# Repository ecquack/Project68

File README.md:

# Project68

Project68 is a Motorola MC68xxx 16/32 bit single board computer with an 8 bit PIC18 co-processor. 

My goal was to do something interesting with the tube of factory new 68008 CPUs that I've been hoarding for 25 years, 
so I have designed a useful self contained 68K computer using a minumum number of components and special tools.

The system connects directly to a monitor and keyboard and does not require a host computer.

This project is at an early stage of development, but it is intended to run uCLinux 4.4.

Special thanks to [*crmaykish*](https://github.com/crmaykish), creator of the [Mackerel-68K](https://github.com/crmaykish/mackerel-68k) project.

## Project68 features

- MC68008FN8 CPU clocked at 7.16 mHz
- 4 megabytes of SRAM
- Optional overclocking to 14.31818 mHz
- PIC18F87J11 co-processor clocked at 14.31818 mHz (57.27 mHz internal w/4X PLL)
- 80x25 character monochrome ASCII video display (NTSC composite video)
- PS/2 keyboard interface
- TTL/USB serial port
- micro-SD card socket
- Audio Speaker for ASCII “bell” sound
- **No PAL/GAL/CPLD/FPGA programmable logic required**
- Only two LVTTL parts required.
- Expansion ports for a dual serial card and a non-volatile RTC

## OPERATING REQUIREMENTS

- TV or Monitor with composite video input (NTSC)
- PS/2 keyboard
- 5V 1A power supply with USB-C cable (phone charger)
- SD card with uCLinux image

## CPU

The CPU is the 8 bit external bus version of the 68K, the MC68008FN8. It comes in the larger 52 pin PLCC package which can address up to 4 megabytes of memory. The CPU is socketed on the board so that you can use an automated assembly service such as JLC PCB or PCBWAY for all the soldering if you prefer. This is a 16/32 bit CPU internally with a narrow external bus which allows using byte wide external memories.

The parts I have are rated at 8mHz, but 10mHz parts are also available (MC68000FN10). In order to provide an NTSC video clock, the processor runs at ~7.16mHz. Either speed part can (usually) be successfully overclocked to ~14.318mHz without issue. An overclocking jumper is provided if you feel the need for speed.

## MEMORY

The system has four megabytes of memory. It uses a single 32 megabit 4Mx8 55ns SRAM chip. This fills the *entire* available address space with SRAM. There is no separate FLASH, EPROM, or ROM memory, no address decoding of any kind,  no special address hardware at reset, and no traditional memory mapped I/O. Just an unbroken sea of RAM from 0-0x3FFFFF and a simple _DTACK generator. 

The SRAM part is a fairly pricey Renesas RMLV3216AGSA-5S2 sourced from Digikey. You can also use the pin compatible Alliance AS6C6416-55TIN from Mouser which is a 64 megabit part, which is actually cheaper, but you will only be utilizing half the memory.

The memory and the PIC18 run at 3.3 volts (there is an LDO regulator on the board). The 5 volt MC68008  has a logic high level of 2.4 volts, which might be safe to use with these parts. I may end up using level shifters, but they eat 20 nanoseconds from the bus cycle. Stay tuned for my experimental results.

## CO-PROCESSSOR

The PIC18F87J11 microcontroller comes in an 80 pin TQFP package. This part was chosen because it has enough GPIO pins to emulate the entire MC68008 bus. It has 128K of FLASH memory, and just under 4K of on chip SRAM.

**The PIC18 co-processor provides all the main processor’s I/O using soft-DMA.** When it is time to transfer data to or from the processor, the co-processor requests the bus from the 68008. When the bus is granted, it uses bit-banging DMA to read and write the SRAM. A few specific addresses in the memory space are designated as I/O command and status registers and are interpreted as such by the co-processor to provide low level BIOS functions for the console, serial port, and SD card. 

At power up the co-processor asserts _HALT and _RESET and then copies up to 64K of BIOS into the SRAM from the upper half of FLASH memory that’s built into the PIC18. It then releases the 68K bus and the MC68008 starts.

## VIDEO DISPLAY

**The co-processor is also responsible for generating the 80x25 video display.** This is done with a *really* tight  horizontal sync interrupt handler written in assembly language. It uses an interleaved character FLASH lookup table with an 8x8 pixel font. One EUSART on the PIC18 is used as a video shift register (nice!), which makes it possible to clock pixels out once per instruction cycle.

Roughly half of the PIC18's SRAM (2K) is dedicated to the video display.

The physical video interface consists of two output pins and a two resistor network that is connected to an RCA jack. One pin is the output of the synchronous serial transmitter, and the other is the software generated sync line, used for both horizontal and vertical sync.

The video display is not interlaced and does not include a colorburst. The 8x8 ROM font consists of the standard printable ASCII characters (codes 32-126), plus a number of special characters (codes 0-31 and 127). The upper 128 characters are reverse video of the lower 128 characters, which is used to generate the cursor. There are no fancy effects like blink, underscore, or dim. There are no code page 437 special characters.

Most of the co-processor's time is spent generating video. There is a short horizontal blanking period at the end of each line, and there is a longer vertical blanking interval at the end of each video field during which the processor is free to perform other tasks. All video generation (and PS/2 keyboard processing) takes place inside the interrupt handler.

Note that it should be possible to run a PAL monitor instead of NTSC by simply adjusting the timing #DEFINE statements in the beginning of *80columnvideo.h*.
I do not have a monitor that accepts PAL video to test this with.

## PS/2 INTERFACE

The system uses the PIC18 MSSP (synchronous serial port) in slave mode with an assembly language interrupt handler to interface to the PS/2 keyboard. 
The interrupt handler runs during horizontal blanking, and always takes the same number of clock cycles to run, no matter which code path is taken, to avoid disturbing the video output. 

When characters arrive on the PS/2 keyboard or serial port, the co-processor requests the bus, and stores the received characters into a software FIFO in SRAM.

## SD CARD

The SD card socket is connected to the PIC18 over the shared SPI bus. 512 bytes of PIC18 SRAM is reserved to store a single block of data to/from the SD card. 

## BIOS

The BIOS provides a few functions to access the console, the serial port, and the SD card. It also loads and starts Linux from the SD card. Additional functions could be added, for example, to copy the entire screen buffer to and from memory, give control over the PWM audio output beyond the fixed "beep", or to support additional SPI devices such as a non-volatile real time clock. 

## TIMER INTERRUPT

The vertical blanking signal serves as a periodic timer interrupt (60 hertz) to the 68008. This is used by the BIOS for communication and by the Linux kernel for timekeeping and task switching. 

## USB/TTL SERIAL PORT

A CH340N provides a very basic serial port connection to a USB host system. The USB C connector also provides power to the board. There is also a header with jumpers that allow the TTL serial lines to be disconnected from the USB chip and used directly. 

## EXPANSION PORTS

There are two main expansion ports. Each has power, SPI bus, it's own SPI chip select, it's own interrupt line, and two GPIO pins. My intention is to use an SPI DUAL UART on one port and an SPI RTC on the other. Supporting these will require additions to the BIOS. The interrupt line and the chip select can be used as GPIOs if the SPI bus is not used, but MISO, MOSI, and SCLK are shared with the SD card socket and cannot be reassigned.

There is also a third expansion port which brings out the three unused PIC18 GPIO pins, power, and ground. Two of these pins are on port B and can be used as interrupt sources.

## ICSP PORT

For programming the PIC MCU, this 6 pin connector contains PGD, PGC, _MCLR, +5V, and GND.

## PERFORMANCE NOTES

The current system was designed to see how simply a complete 68K computer system could be made, and it uses a minimum number of parts for a system that has its own video and keyboard interfaces. By adding just a few chips you can dramatically increase the performance of the system.

For higher overall system performance you could use a second smaller PIC18 (such as a PIC18F26K22) dedicated to generating video. Right now there is an I/O bottleneck because I/O operations are only performed during video blanking.

A decoded address that causes an interrupt on the PIC18 would eliminate the need for the PIC18 to poll the MC68008's memory. Again, this would increase performance but it would add chips to the design and eat into the memory address space. Two 74HCT30s and a 74HCT00 would suffice, and would eat only 64 bytes from the memory map. 

## BUILD REQUIREMENTS
 
- PIC programmer for initial programming (you can build a very simple bit-banging programmer using a repurposed Arduino)
- Computer system with MicroSD card interface for preparing the SD card.
- CCS PICC C Compiler (optional - pre-built binaries are available)*
- X86 Linux system (optional - a pre-built binary is available)
- KiCAD (optional - Gerber files are provided)

*note that there is a 45 day free trial of this compiler.

## Pre-assembled boards

I started out with a tube full of sixteen 68008 parts that I got from a Motorola rep back in the '90s. I'm keeping a few chips for myself and my friends, but 
I may have a few pre-assembled boards complete with CPUs and SD cards for sale at some point. 

Note that the MC68008FN is no longer in production, but at this time (August, 2025) it is not difficult to find them on eBay for around USD$30 with shipping. 

## PROJECT STATUS

The schematic capture and layout of the first version is complete. I'll order the blank boards and stencil from JLCPCB next.

I wrote the PIC18 80 column video code and the PS/2 keyboard handler code back in 2010 and posted them to the CCS C compiler forum. They were tested on a single sided PIC18F26J11 board that I milled on my CNC machine back in the day.

Once the layout is complete I plan to have a pair of assembled boards made for my by JLCPCB.

After that, the next debugging steps are:

0. Blink the LED
1. Get the video display running
2. test the keyboard port
3. bit-bang the memory interface to read and write from the SRAM
4. load a small test program into the 68K and start it
5. read and write a block from the SD card

Then comes the work of writing the BIOS and building the linux image.

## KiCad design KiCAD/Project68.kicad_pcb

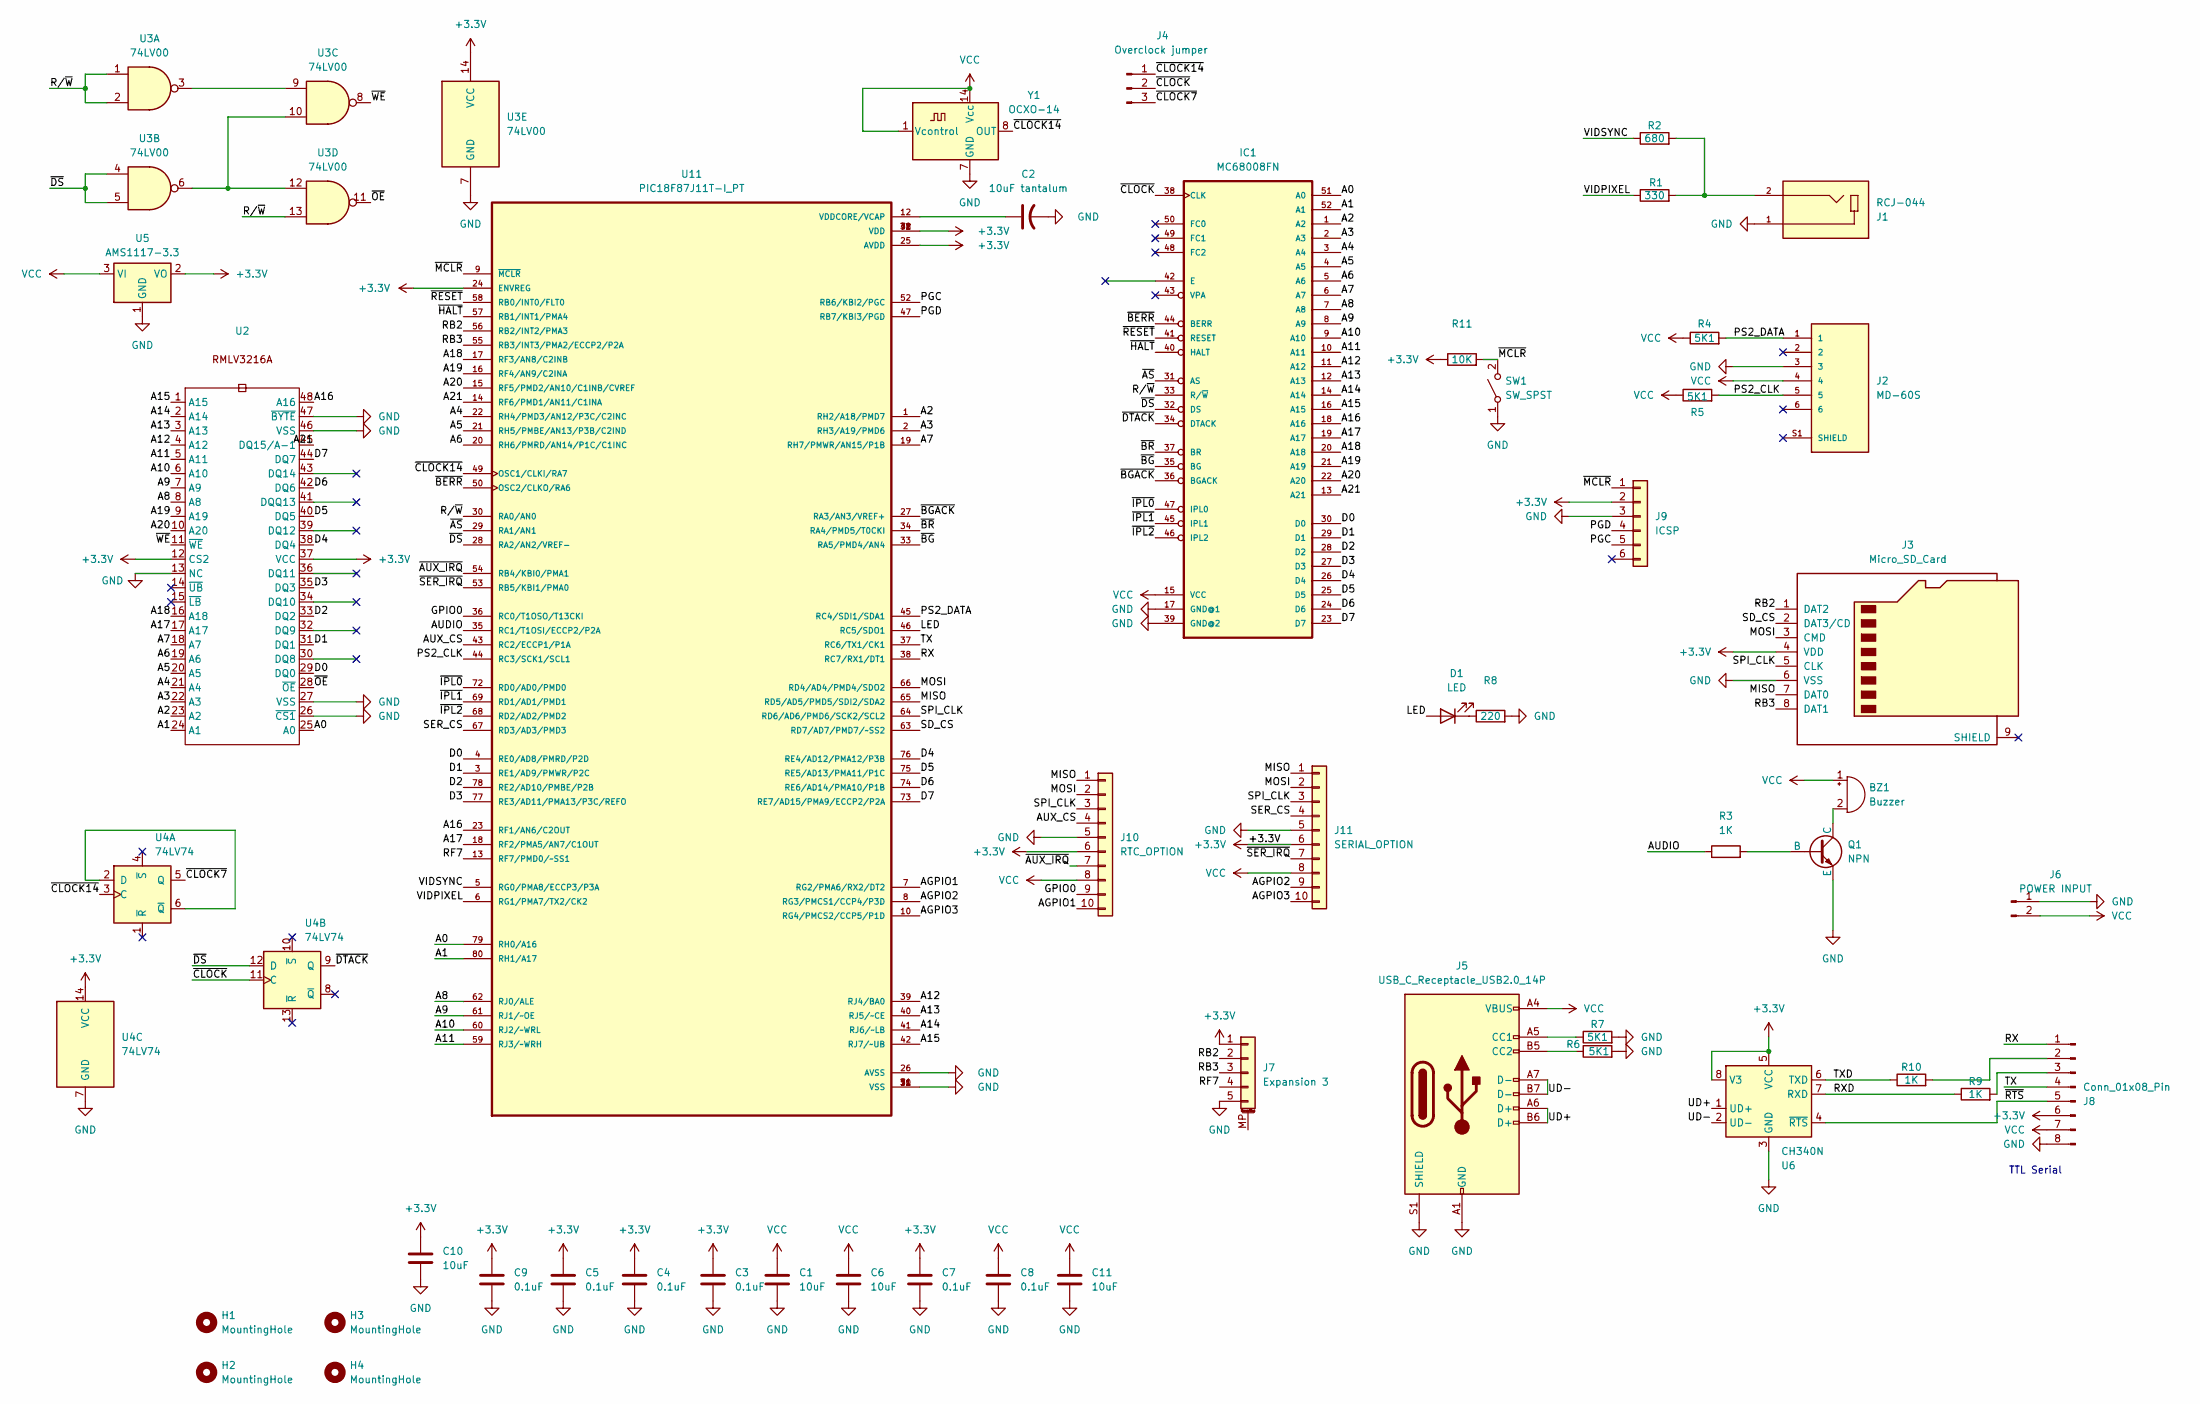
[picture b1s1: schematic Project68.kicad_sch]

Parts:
BZ1: Buzzer; MURATA
C1, C6, C10, C11: 10uF; C_1206_3216Metric
C2: 10uF tantalum; C_1206_3216Metric
C3, C4, C5, C7, C8, C9: 0.1uF; C_1206_3216Metric
D1: LED; LED_1206_3216Metric
H1, H2, H3, H4: MountingHole; MountingHole_3.2mm_M3
IC1: MC68008FN; PLCC52-S
J1: RCJ-044; CUI_RCJ-044; PARTREV 1.02
J2: MD-60S; CUI_MD-60S; PARTREV 02/18/2022
J3: Micro_SD_Card; microSD_HC_Molex_47219-2001
J4: Overclock jumper; PinHeader_1x03_P2.54mm_Vertical
J5: USB_C_Receptacle_USB2.0_14P; USB_C_Receptacle_GCT_USB4105-xx-A_16P_TopMnt_Horizontal
J6: POWER INPUT; PinHeader_1x02_P2.54mm_Vertical
J7: Expansion 3; PinHeader_1x05_P2.54mm_Vertical
J8: Conn_01x08_Pin; PinHeader_1x08_P2.54mm_Vertical
J9: ICSP; PinHeader_1x06_P2.54mm_Vertical
J10: RTC_OPTION; PinHeader_1x10_P2.54mm_Vertical
J11: SERIAL_OPTION; PinHeader_1x10_P2.54mm_Vertical
Q1: NPN; SOT-23-3
R1: 330; R_1206_3216Metric
R2: 680; R_1206_3216Metric
R3, R9, R10: 1K; R_1206_3216Metric
R4, R5, R6, R7: 5K1; R_1206_3216Metric
R8: 220; R_1206_3216Metric
R11: 10K; R_1206_3216Metric
SW1: SW_SPST; SW_Push_1P1T_NO_CK_KMR2
U2: TSOP-I-48_18.4x12mm_P0.5mm
U3: 74LV00; SOIC-14_3.9x8.7mm_P1.27mm
U4: 74LV74; SOIC-14_3.9x8.7mm_P1.27mm
U5: AMS1117-3.3; SOT-223-3_TabPin2
U6: CH340N; SOP-8_3.9x4.9mm_P1.27mm
U11: PIC18F87J11T-I_PT; QFP50P1400X1400X120-80N
Y1: OCXO-14; Oscillator_DIP-14

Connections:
+3.3V: C3.1, C4.1, C5.1, C7.1, C9.1, C10.1, J3.4 (VDD), J7.1, J8.6, J9.2, J10.6, J11.6, R11.1, U2.12 (CS2), U2.37 (VCC), U3.14 (VCC), U4.14 (VCC), U5.2 (VO), U6.5 (VCC), U6.8 (V3), U11.24 (ENVREG), U11.25 (AVDD), U11.32 (VDD), U11.48 (VDD), U11.71 (VDD)
/A0: IC1.51 (A0), U2.25 (A0), U11.79 (RH0/A16)
/A1: IC1.52 (A1), U2.24 (A1), U11.80 (RH1/A17)
/A2: IC1.1 (A2), U2.23 (A2), U11.1 (RH2/A18/PMD7)
/A3: IC1.2 (A3), U2.22 (A3), U11.2 (RH3/A19/PMD6)
/A4: IC1.3 (A4), U2.21 (A4), U11.22 (RH4/PMD3/AN12/P3C/C2INC)
/A5: IC1.4 (A5), U2.20 (A5), U11.21 (RH5/PMBE/AN13/P3B/C2IND)
/A6: IC1.5 (A6), U2.19 (A6), U11.20 (RH6/PMRD/AN14/P1C/C1INC)
/A7: IC1.6 (A7), U2.18 (A7), U11.19 (RH7/PMWR/AN15/P1B)
/A8: IC1.7 (A8), U2.8 (A8), U11.62 (RJ0/ALE)
/A9: IC1.8 (A9), U2.7 (A9), U11.61 (RJ1/~OE)
/A10: IC1.9 (A10), U2.6 (A10), U11.60 (RJ2/~WRL)
/A11: IC1.10 (A11), U2.5 (A11), U11.59 (RJ3/~WRH)
/A12: IC1.11 (A12), U2.4 (A12), U11.39 (RJ4/BA0)
/A13: IC1.12 (A13), U2.3 (A13), U11.40 (RJ5/~CE)
/A14: IC1.14 (A14), U2.2 (A14), U11.41 (RJ6/~LB)
/A15: IC1.16 (A15), U2.1 (A15), U11.42 (RJ7/~UB)
/A16: IC1.18 (A16), U2.48 (A16), U11.23 (RF1/AN6/C2OUT)
/A17: IC1.19 (A17), U2.17 (A17), U11.18 (RF2/PMA5/AN7/C1OUT)
/A18: IC1.20 (A18), U2.16 (A18), U11.17 (RF3/AN8/C2INB)
/A19: IC1.21 (A19), U2.9 (A19), U11.16 (RF4/AN9/C2INA)
/A20: IC1.22 (A20), U2.10 (A20), U11.15 (RF5/PMD2/AN10/C1INB/CVREF)
/A21: IC1.13 (A21), U2.45 (DQ15/A-1), U11.14 (RF6/PMD1/AN11/C1INA)
/AGPIO1: J10.10, U11.7 (RG2/PMA6/RX2/DT2)
/AGPIO2: J11.9, U11.8 (RG3/PMCS1/CCP4/P3D)
/AGPIO3: J11.10, U11.10 (RG4/PMCS2/CCP5/P1D)
/AUDIO: R3.1, U11.35 (RC1/T1OSI/ECCP2/P2A)
/AUX_CS: J10.4, U11.43 (RC2/ECCP1/P1A)
/D0: IC1.30 (D0), U2.29 (DQ0), U11.4 (RE0/AD8/PMRD/P2D)
/D1: IC1.29 (D1), U2.31 (DQ1), U11.3 (RE1/AD9/PMWR/P2C)
/D2: IC1.28 (D2), U2.33 (DQ2), U11.78 (RE2/AD10/PMBE/P2B)
/D3: IC1.27 (D3), U2.35 (DQ3), U11.77 (RE3/AD11/PMA13/P3C/REFO)
/D4: IC1.26 (D4), U2.38 (DQ4), U11.76 (RE4/AD12/PMA12/P3B)
/D5: IC1.25 (D5), U2.40 (DQ5), U11.75 (RE5/AD13/PMA11/P1C)
/D6: IC1.24 (D6), U2.42 (DQ6), U11.74 (RE6/AD14/PMA10/P1B)
/D7: IC1.23 (D7), U2.44 (DQ7), U11.73 (RE7/AD15/PMA9/ECCP2/P2A)
/GPIO0: J10.9, U11.36 (RC0/T1OSO/T13CKI)
/LED: D1.2 (A), U11.46 (RC5/SDO1)
/MISO: J3.7 (DAT0), J10.1, J11.1, U11.65 (RD5/AD5/PMD5/SDI2/SDA2)
/MOSI: J3.3 (CMD), J10.2, J11.2, U11.66 (RD4/AD4/PMD4/SDO2)
/PGC: J9.5, U11.52 (RB6/KBI2/PGC)
/PGD: J9.4, U11.47 (RB7/KBI3/PGD)
/PS2_CLK: J2.5, R5.2, U11.44 (RC3/SCK1/SCL1)
/PS2_DATA: J2.1, R4.2, U11.45 (RC4/SDI1/SDA1)
/RB2: J3.1 (DAT2), J7.2, U11.56 (RB2/INT2/PMA3)
/RB3: J3.8 (DAT1), J7.3, U11.55 (RB3/INT3/PMA2/ECCP2/P2A)
/RF7: J7.4, U11.13 (RF7/PMD0/~SS1)
/RX: J8.1, U11.38 (RC7/RX1/DT1)
/RXD: R9.1, U6.7 (RXD)
/R/~W: IC1.33 (R/~W), U3.1, U3.2, U3.13, U11.30 (RA0/AN0)
/SD_CS: J3.2 (DAT3/CD), U11.63 (RD7/AD7/PMD7/~SS2)
/SER_CS: J11.4, U11.67 (RD3/AD3/PMD3)
/SPI_CLK: J3.5 (CLK), J10.3, J11.3, U11.64 (RD6/AD6/PMD6/SCK2/SCL2)
/TX: J8.4, U11.37 (RC6/TX1/CK1)
/TXD: R10.1, U6.6 (TXD)
/UD+: J5.A6 (D+), J5.B6 (D+), U6.1 (UD+)
/UD-: J5.A7 (D-), J5.B7 (D-), U6.2 (UD-)
/VIDPIXEL: R1.1, U11.6 (RG1/PMA7/TX2/CK2)
/VIDSYNC: R2.1, U11.5 (RG0/PMA8/ECCP3/P3A)
/~AS: IC1.31 (AS), U11.29 (RA1/AN1)
/~AUX_IRQ: J10.7, U11.54 (RB4/KBI0/PMA1)
/~BERR: IC1.44 (BERR), U11.50 (OSC2/CLKO/RA6)
/~BGACK: IC1.36 (BGACK), U11.27 (RA3/AN3/VREF+)
/~BG: IC1.35 (BG), U11.33 (RA5/PMD4/AN4)
/~BR: IC1.37 (BR), U11.34 (RA4/PMD5/T0CKI)
/~CLOCK7: J4.3, U4.5 (Q)
/~CLOCK14: J4.1, U4.3 (C), U11.49 (OSC1/CLKI/RA7), Y1.8 (OUT)
/~CLOCK: IC1.38 (CLK), J4.2, U4.11 (C)
/~DS: IC1.32 (DS), U3.4, U3.5, U4.12 (D), U11.28 (RA2/AN2/VREF-)
/~DTACK: IC1.34 (DTACK), U4.9 (Q)
/~HALT: IC1.40 (HALT), U11.57 (RB1/INT1/PMA4)
/~IPL0: IC1.47 (IPL0), U11.72 (RD0/AD0/PMD0)
/~IPL1: IC1.45 (IPL1), U11.69 (RD1/AD1/PMD1)
/~IPL2: IC1.46 (IPL2), U11.68 (RD2/AD2/PMD2)
/~MCLR: J9.1, R11.2, SW1.2 (B), U11.9 (~MCLR)
/~OE: U2.28 (~OE), U3.11
/~RESET: IC1.41 (RESET), U11.58 (RB0/INT0/FLT0)
/~RTS: J8.5, U6.4 (~RTS)
/~SER_IRQ: J11.7, U11.53 (RB5/KBI1/PMA0)
/~WE: U2.11 (~WE), U3.8
GND: C1.2, C2.2, C3.2, C4.2, C5.2, C6.2, C7.2, C8.2, C9.2, C10.2, C11.2, IC1.17 (GND@1), IC1.39 (GND@2), J1.1, J2.3, J3.6 (VSS), J5.A1 (GND), J5.A12 (GND), J5.B1 (GND), J5.B12 (GND), J5.S1 (SHIELD), J6.1, J7.5, J8.8, J9.3, J10.5, J11.5, Q1.3 (E), R6.2, R7.2, R8.2, SW1.1 (A), U2.13 (NC), U2.26 (~CS1), U2.27 (VSS), U2.46 (VSS), U2.47 (~BYTE), U3.7 (GND), U4.7 (GND), U5.1 (GND), U6.3 (GND), U11.11 (VSS), U11.26 (AVSS), U11.31 (VSS), U11.51 (VSS), U11.70 (VSS), Y1.7 (GND)
unnamed: BZ1.2 (-), Q1.1 (C)
unnamed: D1.1 (K), R8.1
unnamed: J1.2, R1.2, R2.2
unnamed: J5.A5 (CC1), R7.1
unnamed: J5.B5 (CC2), R6.1
unnamed: J8.2, R10.2
unnamed: J8.3, R9.2
unnamed: Q1.2 (B), R3.2
unnamed: U3.3, U3.9
unnamed: U3.6, U3.10, U3.12
unnamed: U4.2 (D), U4.6 (~Q)
unnamed: C2.1, U11.12 (VDDCORE/VCAP)
VCC: BZ1.1 (+), C1.1, C6.1, C8.1, C11.1, IC1.15 (VCC), J2.4, J5.A4 (VBUS), J5.A9 (VBUS), J5.B4 (VBUS), J5.B9 (VBUS), J6.2, J8.7, J10.8, J11.8, R4.1, R5.1, U5.3 (VI), Y1.1 (Vcontrol), Y1.14 (Vcc)

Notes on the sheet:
TTL Serial

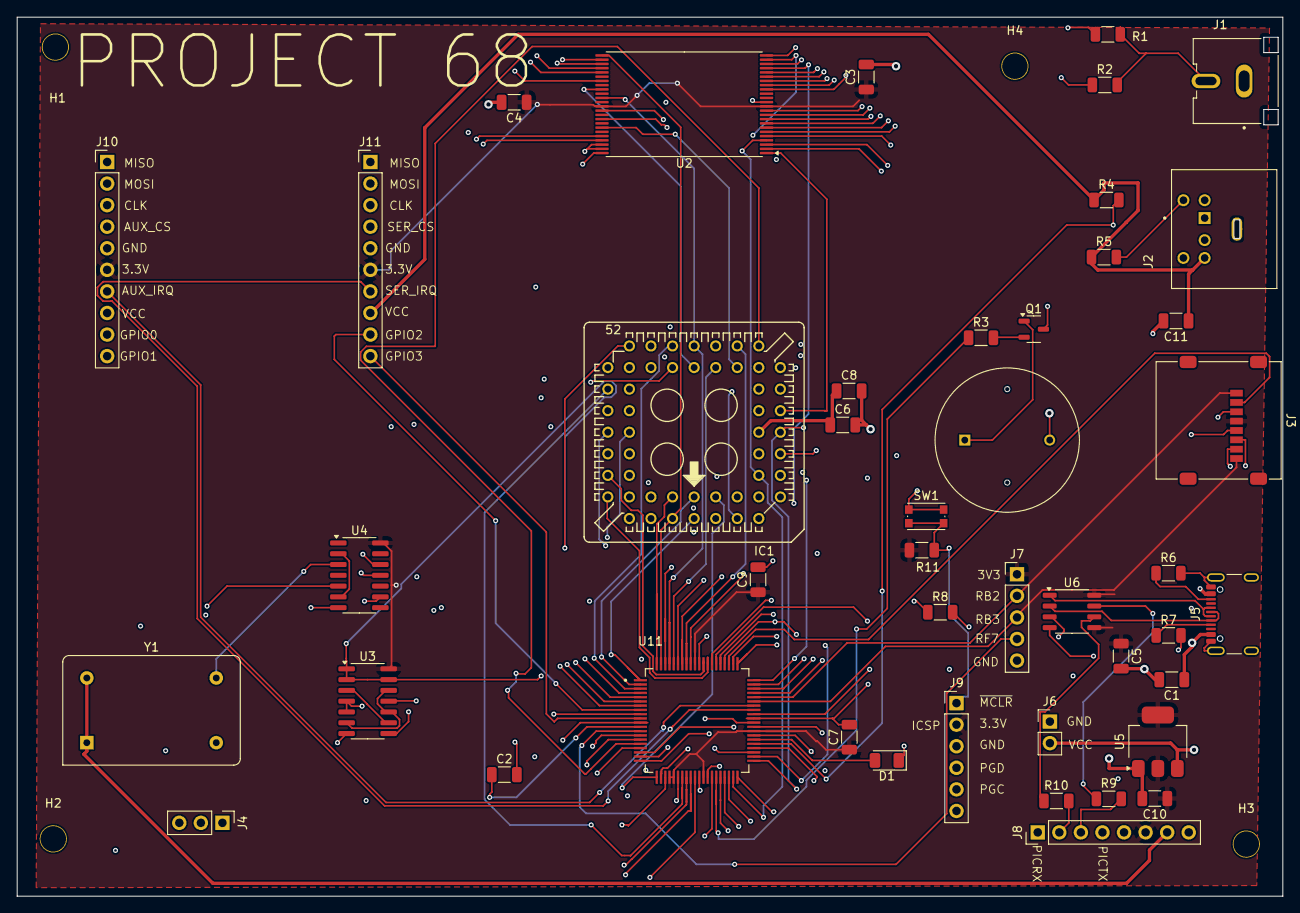
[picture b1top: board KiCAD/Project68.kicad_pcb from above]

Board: 4 copper layers, 149.1 x 103.5 mm, 49 parts (0 on the bottom side), 94 nets.

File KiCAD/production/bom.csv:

Designator,Footprint,Quantity,Value,LCSC Part #
BZ1,MURATA,1,Buzzer,
C2,1206,1,10uF tantalum,
D1,1206,1,LED,
IC1,PLCC52-S,1,MC68008FN,
J1,CUI_RCJ-044,1,RCJ-044,
J10,PinHeader_1x10_P2.54mm_Vertical,1,RTC_OPTION,
J11,PinHeader_1x10_P2.54mm_Vertical,1,SERIAL_OPTION,
J2,CUI_MD-60S,1,MD-60S,
J3,microSD_HC_Molex_47219-2001,1,Micro_SD_Card,
J4,PinHeader_1x03_P2.54mm_Vertical,1,Overclock jumper,
J5,USB_C_Receptacle_GCT_USB4105-xx-A_16P_TopMnt_Horizontal,1,USB_C_Receptacle_USB2.0_14P,
J6,PinHeader_1x02_P2.54mm_Vertical,1,POWER INPUT,
J8,PinHeader_1x08_P2.54mm_Vertical,1,Conn_01x08_Pin,
J9,PinHeader_1x06_P2.54mm_Vertical,1,ICSP,
Q1,SOT-23-3,1,NPN,
R1,1206,1,330,
"R10, R3, R9",1206,3,1K,
R2,1206,1,680,
"R4, R5, R6, R7",1206,4,5K1,
R8,1206,1,220,
U11,QFP50P1400X1400X120-80N,1,PIC18F87J11T-I_PT,
U2,TSOP-I-48_18.4x12mm_P0.5mm,1,~,
U3,SOIC-14_3.9x8.7mm_P1.27mm,1,74LV00,
U4,SOIC-14_3.9x8.7mm_P1.27mm,1,74LV74,
U5,SOT-223-3_TabPin2,1,AMS1117-3.3,
U6,SOP-8_3.9x4.9mm_P1.27mm,1,CH340N,
Y1,Oscillator_DIP-14,1,OCXO-14,

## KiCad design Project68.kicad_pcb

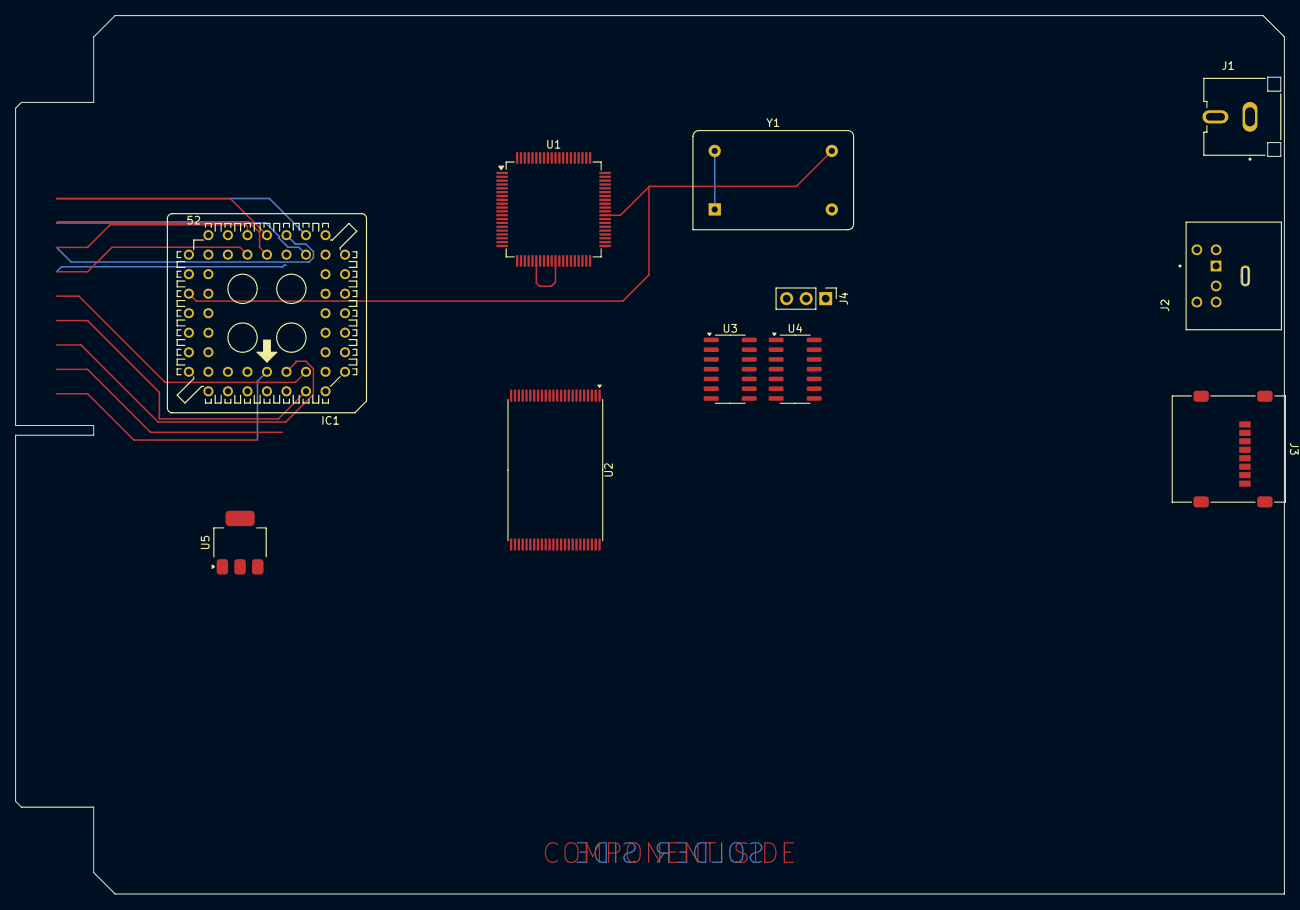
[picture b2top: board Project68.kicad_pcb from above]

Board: 4 copper layers, 165.1 x 114.3 mm, 11 parts (0 on the bottom side), 55 nets.

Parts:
IC1: MC68008FN; PLCC52-S
J1: RCJ-044; CUI_RCJ-044
J2: MD-60S; CUI_MD-60S
J3: Micro_SD_Card; microSD_HC_Molex_47219-2001
J4: Conn_01x03_Pin; PinHeader_1x03_P2.54mm_Vertical
U1: PIC18F87K22-xPT; TQFP-80_12x12mm_P0.5mm
U2: TSOP-I-48_18.4x12mm_P0.5mm
U3: 74LS00; SOIC-14_3.9x8.7mm_P1.27mm
U4: 74LS74; SOIC-14_3.9x8.7mm_P1.27mm
U5: AMS1117-3.3; SOT-223-3_TabPin2
Y1: OCXO-14; Oscillator_DIP-14

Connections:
+3.3V: U2.12 (CS2), U2.37 (VCC), U5.2 (VO)
/A0: IC1.51 (A0), U1.79 (RH0/AN23), U2.25 (A0)
/A1: IC1.52 (A1), U1.80 (RH1/AN22), U2.24 (A1)
/A2: IC1.1 (A2), U1.1 (RH2/AN21), U2.23 (A2)
/A3: IC1.2 (A3), U1.2 (RH3/AN20), U2.22 (A3)
/A4: IC1.3 (A4), U1.22 (RH4/AN12), U2.21 (A4)
/A5: IC1.4 (A5), U1.21 (RH5/AN13), U2.20 (A5)
/A6: IC1.5 (A6), U1.20 (RH6/AN14), U2.19 (A6)
/A7: IC1.6 (A7), U1.19 (RH7/AN15), U2.18 (A7)
/A8: IC1.7 (A8), U1.62 (RJ0), U2.8 (A8)
/A9: IC1.8 (A9), U1.61 (RJ1), U2.7 (A9)
/A10: IC1.9 (A10), U1.60 (RJ2), U2.6 (A10)
/A11: IC1.10 (A11), U1.59 (RJ3), U2.5 (A11)
/A12: IC1.11 (A12), U1.39 (RJ4), U2.4 (A12)
/A13: IC1.12 (A13), U1.40 (RJ5), U2.3 (A13)
/A14: IC1.14 (A14), U1.41 (RJ6), U2.2 (A14)
/A15: IC1.16 (A15), U1.42 (RJ7), U2.1 (A15)
/A16: IC1.18 (A16), U1.23 (RF1/AN6), U2.48 (A16)
/A17: IC1.19 (A17), U1.18 (RF2/AN7), U2.17 (A17)
/A18: IC1.20 (A18), U1.17 (RF3/AN8), U2.16 (A18)
/A19: IC1.21 (A19), U1.16 (RF4/AN9), U2.9 (A19)
/A20: IC1.22 (A20), U1.15 (RF5/AN10), U2.10 (A20)
/A21: IC1.13 (A21), U1.14 (RF6/AN11), U2.45 (DQ15/A-1)
/D0: IC1.30 (D0), U1.4 (RE0), U2.29 (DQ0)
/D1: IC1.29 (D1), U1.3 (RE1), U2.31 (DQ1)
/D2: IC1.28 (D2), U1.78 (RE2), U2.33 (DQ2)
/D3: IC1.27 (D3), U1.77 (RE3), U2.35 (DQ3)
/D4: IC1.26 (D4), U1.76 (RE4), U2.38 (DQ4)
/D5: IC1.25 (D5), U1.75 (RE5), U2.40 (DQ5)
/D6: IC1.24 (D6), U1.74 (RE6), U2.42 (DQ6)
/D7: IC1.23 (D7), U1.73 (RE7), U2.44 (DQ7)
/FC0: IC1.50 (FC0), U1.55 (RB3)
/FC1: IC1.49 (FC1), U1.54 (RB4)
/FC2: IC1.48 (FC2), U1.53 (RB5)
/R/~W: IC1.33 (R/~W), U1.30 (RA0/AN0)
/R~W: U3.1, U3.2, U3.13
/~AS: IC1.31 (AS), U1.29 (RA1/AN1), U3.4, U3.5
/~BERR: IC1.44 (BERR), U1.56 (RB2)
/~BGACK: IC1.36 (BGACK), U1.50 (RA6/OSC2)
/~BG: IC1.35 (BG), U1.33 (RA5/AN4)
/~BR: IC1.37 (BR), U1.34 (RA4)
/~CLOCK7: J4.3, U4.5 (Q)
/~CLOCK68K: IC1.38 (CLK), J4.2, U4.11 (C)
/~CLOCK: J4.1, U1.49 (RA7/OSC1), Y1.8 (OUT)
/~DS: IC1.32 (DS), U1.28 (RA2/AN2/Vref-), U4.12 (D)
/~DTACK: IC1.34 (DTACK), U4.9 (Q)
/~HALT: IC1.40 (HALT), U1.57 (RB1)
/~OE: U2.28 (~OE), U3.11
/~RESET: IC1.41 (RESET), U1.58 (RB0)
/~WE: U2.11 (~WE), U3.8
GND: IC1.17 (GND@1), IC1.39 (GND@2), U1.11 (VSS), U1.26 (AVSS), U1.31 (VSS), U1.51 (VSS), U1.70 (VSS), U2.26 (~CS1), U2.27 (VSS), U2.46 (VSS), U2.47 (~BYTE), U5.1 (GND), Y1.7 (GND)
unnamed: U3.3, U3.9
unnamed: U3.6, U3.10, U3.12
unnamed: U4.2 (D), U4.6 (~Q)
VCC: IC1.15 (VCC), U1.25 (AVDD), U1.32 (VDD), U1.48 (VDD), U1.71 (VDD), U5.3 (VI), Y1.1 (Vcontrol), Y1.14 (Vcc)

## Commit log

2025-08-11 schematic has major components placed and most pins named
2025-08-11 wired I/O ports
2025-08-12 grounded NC pin on SRAM
2025-08-12 added status LED
2025-08-12 added 80 column video files
2025-08-13 level shifters & CH340
2025-08-13 moved files around
2025-08-25 began autorouting
2025-09-03 almost ready for production
2025-09-10 added support for 4 bit SD card access
2025-09-12 added daughter card dual serial
